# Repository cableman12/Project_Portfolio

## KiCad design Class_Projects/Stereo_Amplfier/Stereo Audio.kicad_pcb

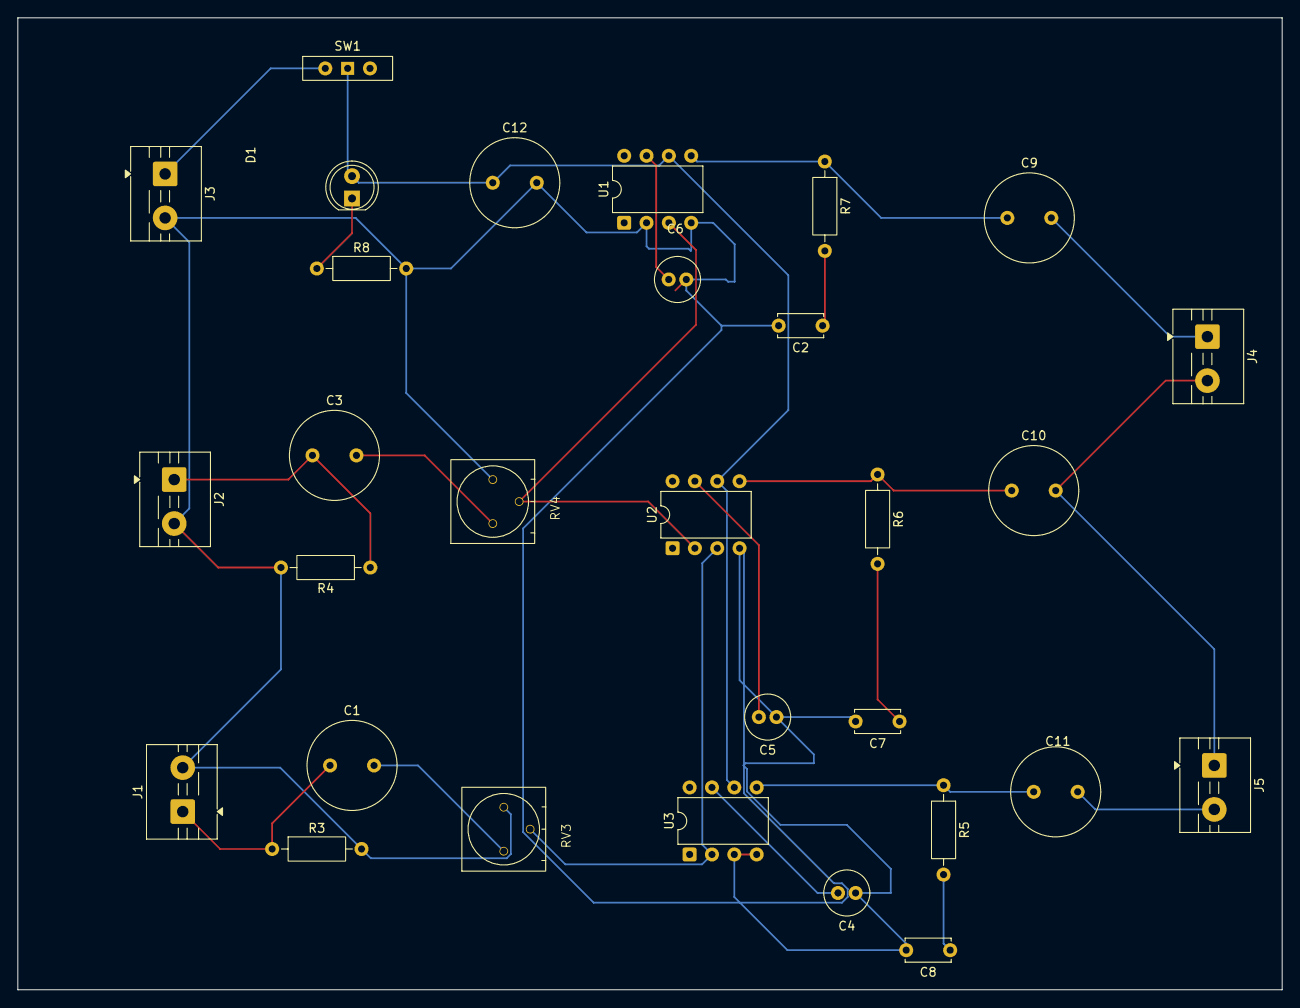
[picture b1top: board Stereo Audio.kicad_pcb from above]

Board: 2 copper layers, 143.8 x 110.5 mm, 30 parts (0 on the bottom side), 22 nets.

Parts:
C1, C3: 4.7 uF; C_Radial_D10.0mm_H16.0mm_P5.00mm
C2, C7: 0.047 uF; C_Disc_D5.0mm_W2.5mm_P5.00mm
C4, C5, C6: 22 uF; C_Radial_D5.0mm_H11.0mm_P2.00mm
C8: 0.047 uf; C_Disc_D5.0mm_W2.5mm_P5.00mm
C9, C10, C11, C12: 470 uF; C_Radial_D10.0mm_H16.0mm_P5.00mm
D1: LED; LED_D5.0mm
J1, J2, J3, J4, J5: Screw_Terminal_01x02; TerminalBlock_MaiXu_MX126-5.0-02P_1x02_P5.00mm
R3, R4: 47k; R_Axial_DIN0207_L6.3mm_D2.5mm_P10.16mm_Horizontal
R5, R6, R7: 10; R_Axial_DIN0207_L6.3mm_D2.5mm_P10.16mm_Horizontal
R8: 1k; R_Axial_DIN0207_L6.3mm_D2.5mm_P10.16mm_Horizontal
RV3, RV4: 10k; POT_stereo
SW1: SW_SPDT; SW_Slide-03_Wuerth-WS-SLTV_10x2.5x6.4_P2.54mm
U1, U2, U3: LM386; DIP-8_W7.62mm

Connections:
+6V: C12.1, D1.2 (A), SW1.1 (A), U1.6 (V+), U2.6 (V+), U3.6 (V+)
GND: C2.2, C4.1, C5.1, C6.2, C7.2, C8.2, C12.2, J1.2, J2.2, J3.2, R3.2, R4.2, R8.2, RV3.3, RV4.3, U1.2 (-), U1.4 (GND), U2.4 (GND), U3.3 (+), U3.4 (GND)
unnamed: C1.2, RV3.1
unnamed: C2.1, R7.2
unnamed: C3.2, RV4.1
unnamed: C7.1, R6.2
unnamed: C8.1, R5.2
unnamed: C9.1, R7.1, U1.5
unnamed: C10.1, R6.1, U2.5
unnamed: C11.1, R5.1, U3.5
unnamed: D1.1 (K), R8.1
unnamed: C1.1, J1.1, R3.1
unnamed: C3.1, J2.1, R4.1
unnamed: J3.1, SW1.2 (B)
unnamed: C9.2, J4.1
unnamed: C10.2, J4.2, J5.1
unnamed: C11.2, J5.2
unnamed: RV4.2, U1.3 (+), U2.2 (-)
unnamed: C6.1, U1.7 (BYPASS)
unnamed: RV3.2, U2.3 (+), U3.2 (-)
unnamed: C5.2, U2.7 (BYPASS)
unnamed: C4.2, U3.7 (BYPASS)

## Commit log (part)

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2026-04-11 Create Read_Me
